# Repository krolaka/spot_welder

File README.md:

# spot_welder
implement hardware spot welder

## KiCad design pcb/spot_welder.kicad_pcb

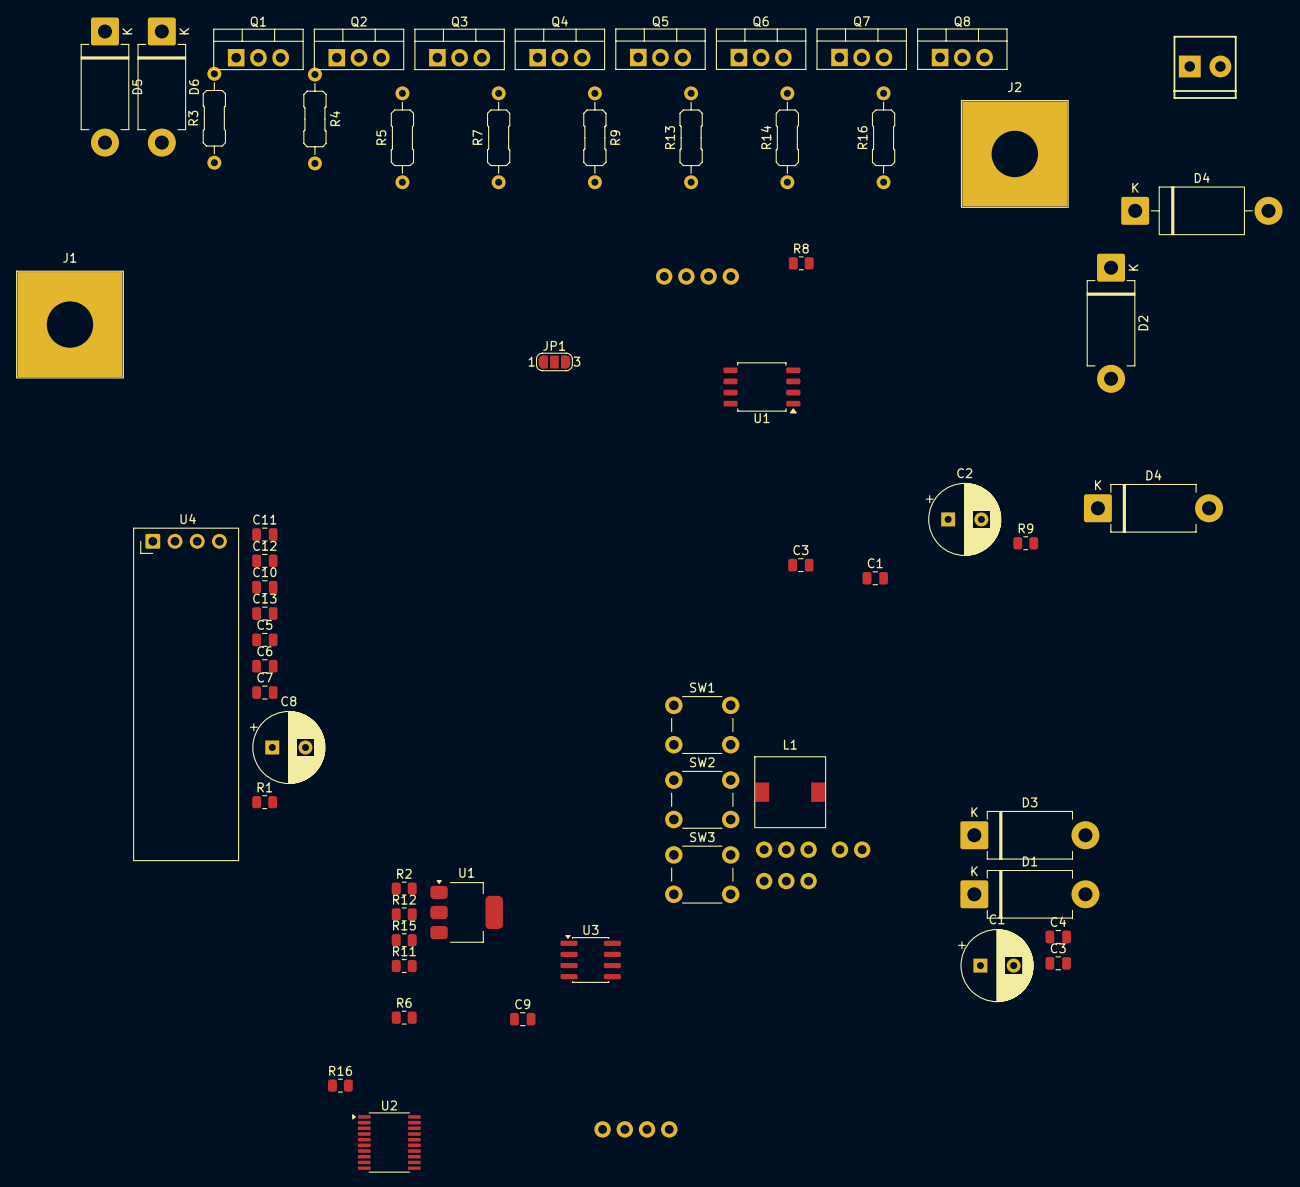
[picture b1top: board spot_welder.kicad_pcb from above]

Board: 2 copper layers, 65 parts (0 on the bottom side), 36 nets, no tracks yet.

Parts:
C1, C4, C5, C9, C10, C11, C12, C13: 100nf; C_0805_2012Metric
C1#2, C8: 25v 68uf; CP_Radial_D8.0mm_P3.80mm
C2: 25v 470uf; CP_Radial_D8.0mm_P3.80mm
C3, C3#2, C6, C7: 10uf; C_0805_2012Metric
D1, D2, D3, D4, D5, D6: 1.5KE15; D_DO-201AD_P12.70mm_Horizontal
D4#2: 1N5822; D_DO-201AD_P15.24mm_Horizontal
J1: Out terminal -; Pad_M5_12x12mm
J2: Battery in -; Pad_M5_12x12mm
J3: Main board connector; 1x04_P2.54mm
J4: 12V supply; ScrewTerminal_1x02_P3.5mm_Horizontal_Black
J5: SWD; 1x03_P2.54mm
J6: Power board connector; 1x04_P2.54mm
J7: UART; 1x03_P2.54mm
J8: FIRE_BTN; 1x02_P2.54mm
JP1: BOOT Jumper; SolderJumper-3_P1.3mm_Open_RoundedPad1.0x1.5mm_NumberLabels
L1: 10uH; L_Sunlord_SWRH0704B
Q1, Q2, Q3, Q4, Q5, Q6, Q7, Q8: HYG016N04LS1P; TO-220-3_Vertical
R1, R9, R11, R12, R16#2: 10k; R_0805_2012Metric
R2, R15: 1k; R_0805_2012Metric
R3, R4, R5, R7, R9#2, R13, R14, R16: 10; R_Axial_DIN0207_L6.3mm_D2.5mm_P10.16mm_Horizontal
R6, R8: 100; R_0805_2012Metric
SW1, SW2, SW3: SW_Push; SW_PUSH_6mm_H5mm
U1: TC4422; SOIC-8_5.3x5.3mm_P1.27mm
U1#2: AMS1117-3.3; SOT-223-3_TabPin2
U2: STM32F030F4Px; TSSOP-20_4.4x6.5mm_P0.65mm
U3: COS27424; SOIC-8_3.9x4.9mm_P1.27mm
U4: oled; ER_OLEDM0.91_1x-I2C

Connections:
+3V3: C5.1, C6.1, C7.1, C8.1, JP1.3 (B), R16#2.2, U1#2.2 (VO), U2.5 (VDDA), U2.16 (VDD), U4.2 (VCC)
+12V: C1#2.1, J3.1, U1#2.3 (VI)
BOOT: R1.1, U2.1 (BOOT0)
DRIVER_ENABLE: J6.4, R8.2
DRIVER_PULSE: J6.3, R6.2
ENABLE: J3.4, U2.12 (PA6)
FIRE_BTN: C13.1, J8.2, U2.9 (PA3)
GND: C1.2, C1#2.2, C2.2, C3.2, C3#2.2, C4.2, C5.2, C6.2, C7.2, C8.2, C9.2, C10.1, C11.2, C12.2, C13.2, D1.2 (A), D2.2 (A), D3.2 (A), D4.2 (A), D5.2 (A), D6.2 (A), J2.1 (Pin_1_1), J3.2, J4.2, J5.3, J6.2, J7.3, J8.1, JP1.1 (A), Q1.3 (S), Q2.3 (S), Q3.3 (S), Q4.3 (S), Q5.3 (S), Q6.3 (S), Q7.3 (S), Q8.3 (S), R2.2, R9.1, R11.1, R12.1, R15.2, SW1.2, SW2.2, SW3.2, U1.4 (GND), U1.5 (GND), U1#2.1 (GND), U2.15 (VSS), U3.3 (GND), U4.1 (GND)
MINUS_BTN: C10.2, SW1.1, U2.6 (PA0)
unnamed: D2.1 (K), D3.1 (K), D5.1 (K), D6.1 (K), J1.1 (Pin_1_1), Q1.2 (D), Q2.2 (D), Q3.2 (D), Q4.2 (D), Q5.2 (D), Q6.2 (D), Q7.2 (D), Q8.2 (D)
unnamed: D4#2.2 (A), J4.1
unnamed: D4.1 (K), U1.6 (OUTPUT), U1.7 (OUTPUT)
unnamed: R9.2, U1.2 (INPUT)
unnamed: JP1.2 (C), R1.2
unnamed: Q1.1 (G), R3.2
unnamed: Q2.1 (G), R4.1
unnamed: Q3.1 (G), R5.2
unnamed: Q4.1 (G), R7.2
unnamed: Q5.1 (G), R9#2.1
unnamed: Q6.1 (G), R13.2
unnamed: Q7.1 (G), R14.2
unnamed: Q8.1 (G), R16.2
unnamed: R8.1, R11.2, U3.1 (EN1), U3.8 (EN2)
unnamed: R2.1, R3.1, R4.2, R5.1, R7.1, U3.7 (OUT1)
unnamed: R9#2.2, R13.1, R14.1, R15.1, R16.1, U3.5 (OUT2)
unnamed: R6.1, R12.2, U3.2 (PWM1), U3.4 (PWM2)
unnamed: C3#2.1, C4.1, L1.2, U3.6 (VCC)
PLUS_BTN: C11.1, SW2.1, U2.7 (PA1)
PULSE: J3.3, U2.14 (PB1)
RESET: C9.1, R16#2.1, U2.4 (NRST)
RX/SDA: J7.2, U2.18 (PA10), U4.4 (SDA)
SELECT_BTN: C12.1, SW3.1, U2.8 (PA2)
SWCLK: J5.2, U2.20 (PA14)
SWDIO: J5.1, U2.19 (PA13)
TX/SCL: J7.1, U2.17 (PA9), U4.3 (SCL)
VDD: C1.1, C2.1, C3.1, D1.1 (K), D4#2.1 (K), J6.1, L1.1, U1.1 (VDD), U1.8 (VDD)
